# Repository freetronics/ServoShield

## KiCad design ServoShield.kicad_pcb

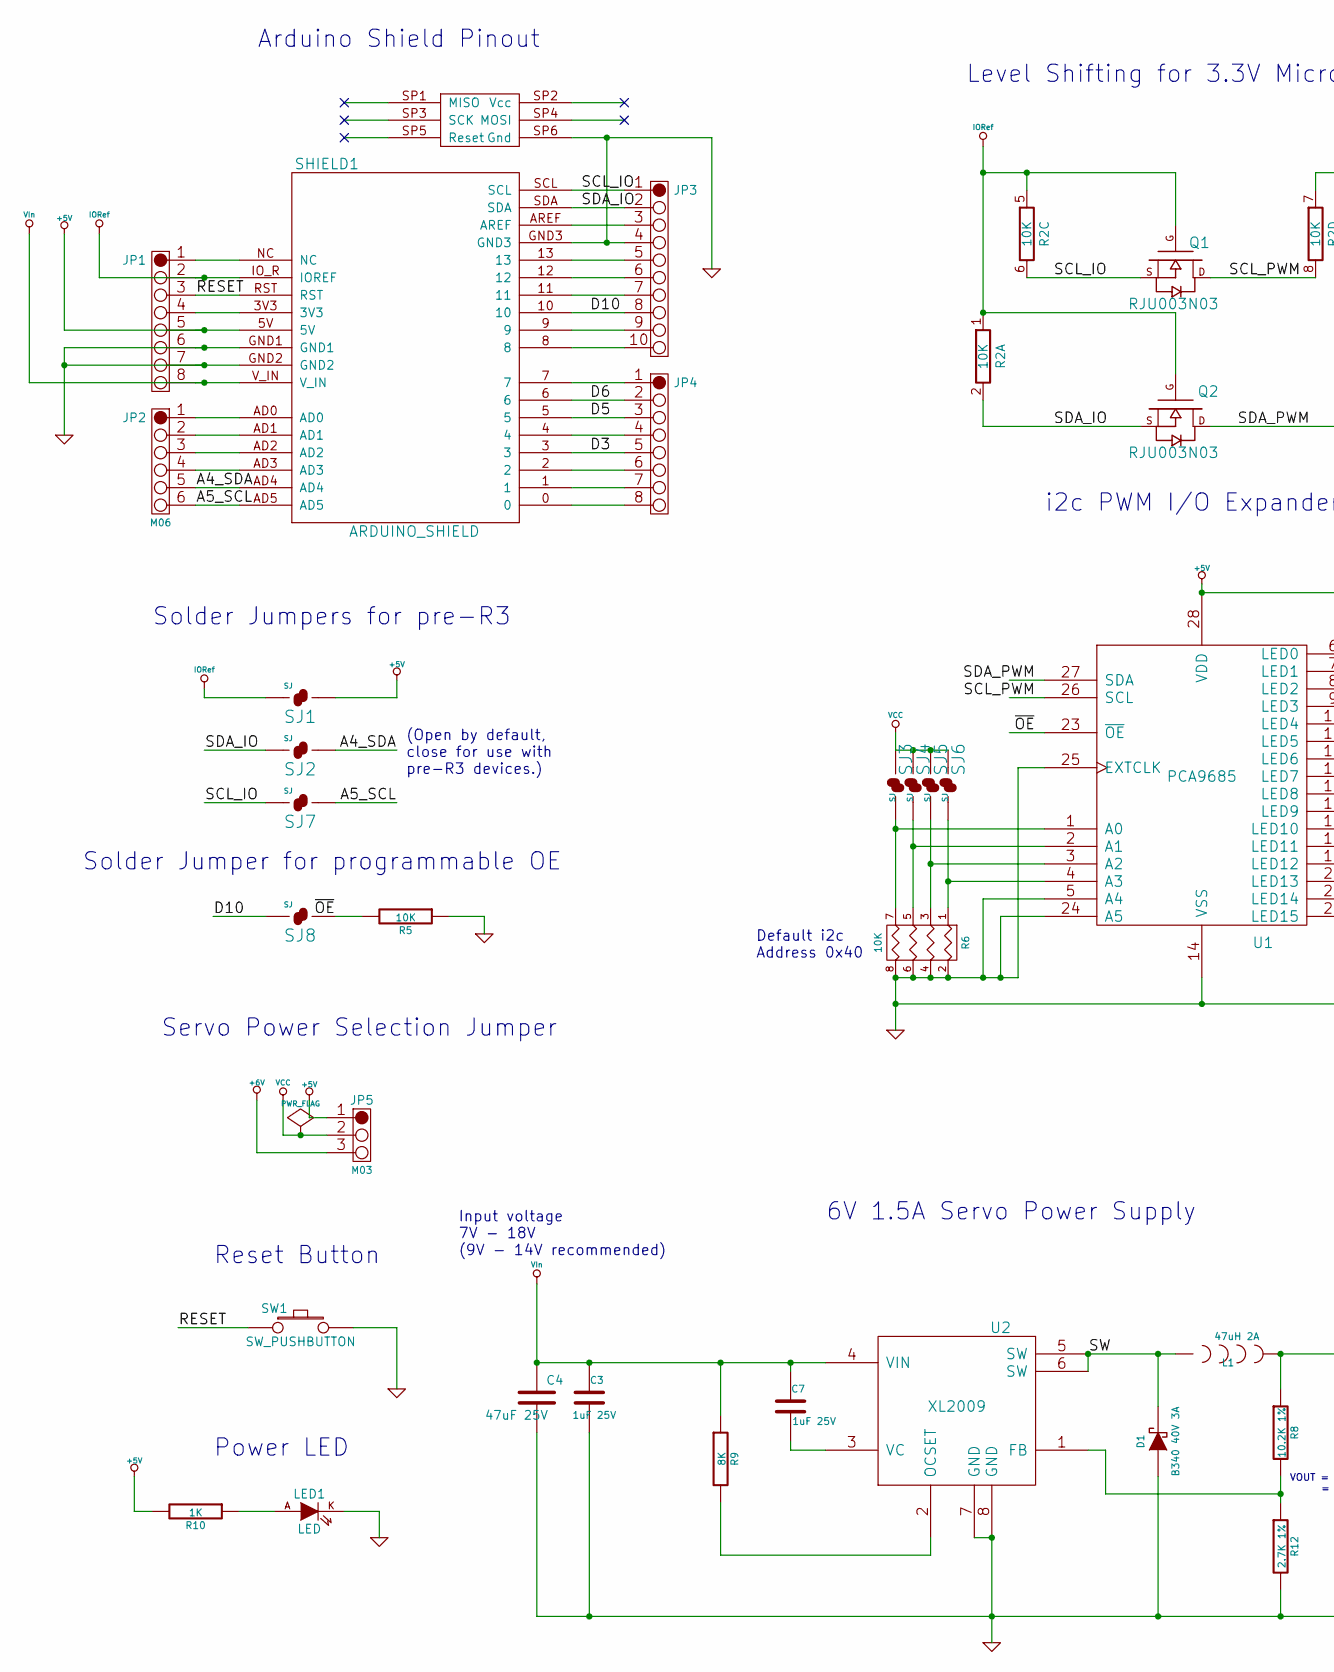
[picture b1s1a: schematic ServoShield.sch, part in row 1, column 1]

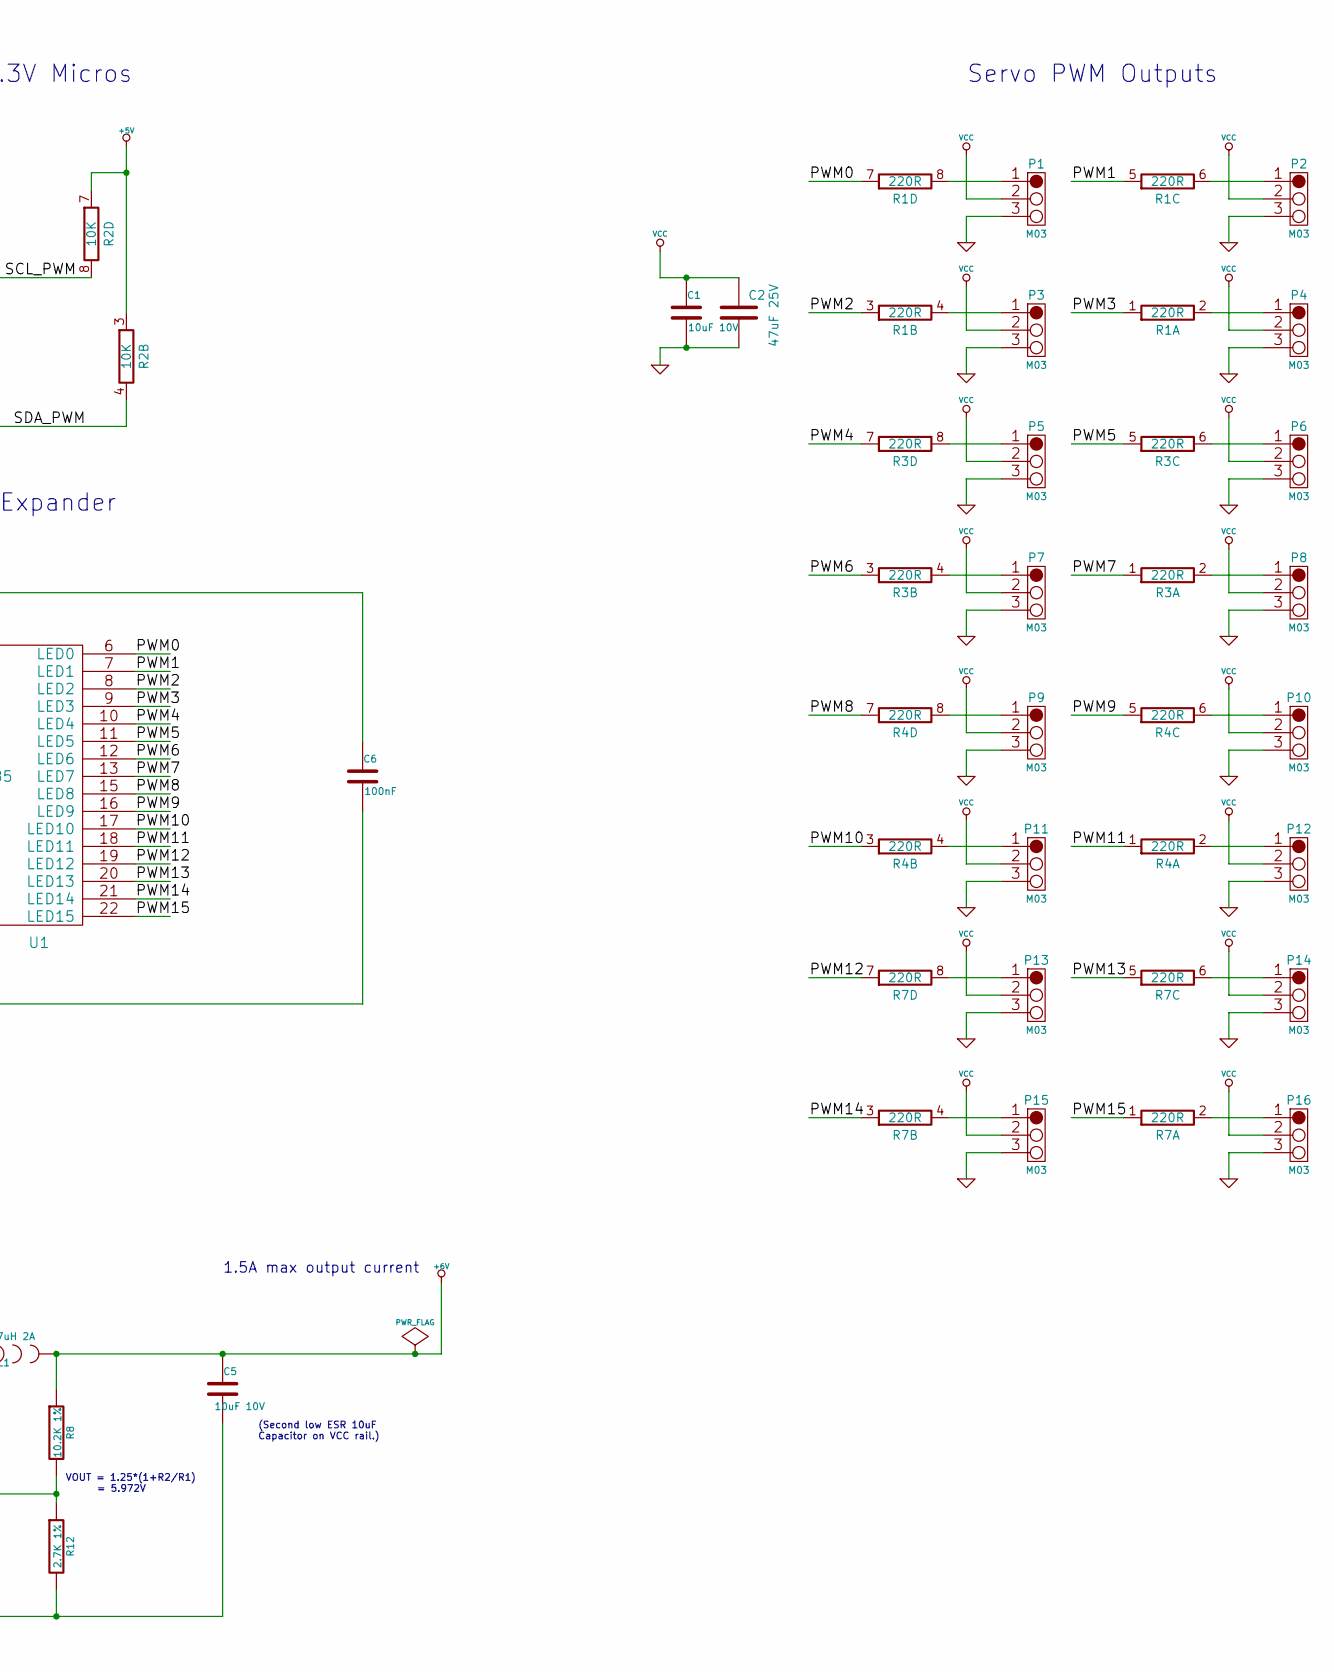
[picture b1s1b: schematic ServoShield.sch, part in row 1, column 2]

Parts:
C1, C5: 10uF 10V; 1210
C2, C4: 47uF 25V; CAP_ELECTRO_SMD_6.6mm
C3, C7: 1uF 25V; 0603_CAP
C6: 100nF; 0603_CAP
D1: B340 40V 3A; DIODE_SMC
JP1, JP4: M08; 1X08
JP2: M06; 1X06
JP3: M10; 1X10
JP5: M03; 1X03
L1: 47uH 2A; IND_CDRH125
LED1: LED; LED-0603
P1, P2, P3, P4, P5, P6, P7, P8, P9, P10, P11, P12, P13, P14, P15, P16: M03; 1X03
Q1, Q2: RJU003N03; SOT323_FET
R1, R3, R4, R7: 220R; RES_CAY16
R2, R6: 10K; RES_CAY16
R5: 10K; 0603
R8: 10.2K 1%; 0603
R9: 8K; 0603
R10: 1K; 0603
R12: 2.7K 1%; 0603
SHIELD1: ARDUINO_SHIELD
SJ1, SJ2, SJ3, SJ4, SJ5, SJ6, SJ7, SJ8: SJ; SJ_OPEN
SW1: SW_PUSHBUTTON; SW_PUSHBUTTON_TINY_2PIN
U1: PCA9685; SSOP28_4mm
U2: XL2009; SO08_4mm

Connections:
+5V: C6.1, JP1.5, JP5.1, R2.3 (7), R2.7, R10.2, SHIELD1.5V, SJ1.2, U1.28 (VDD)
+6V: C5.1, JP5.3, L1.2, R8.1
/A4_SDA: JP2.5, SHIELD1.AD4, SJ2.2
/A5_SCL: JP2.6, SHIELD1.AD5, SJ7.2
/D3: JP4.5, SHIELD1.3
/D5: JP4.3, SHIELD1.5
/D6: JP4.2, SHIELD1.6
/D10: JP3.8, SHIELD1.10, SJ8.1
/PWM0: R1.7, U1.6 (LED0)
/PWM1: R1.5 (7), U1.7 (LED1)
/PWM2: R1.3 (7), U1.8 (LED2)
/PWM3: R1.1 (7), U1.9 (LED3)
/PWM4: R3.7, U1.10 (LED4)
/PWM5: R3.5 (7), U1.11 (LED5)
/PWM6: R3.3 (7), U1.12 (LED6)
/PWM7: R3.1 (7), U1.13 (LED7)
/PWM8: R4.7, U1.15 (LED8)
/PWM9: R4.5 (7), U1.16 (LED9)
/PWM10: R4.3 (7), U1.17 (LED10)
/PWM11: R4.1 (7), U1.18 (LED11)
/PWM12: R7.7, U1.19 (LED12)
/PWM13: R7.5 (7), U1.20 (LED13)
/PWM14: R7.3 (7), U1.21 (LED14)
/PWM15: R7.1 (7), U1.22 (LED15)
/RESET: JP1.3, SHIELD1.RST, SW1.1
/SCL_IO: JP3.1, Q1.S, R2.6 (8), SHIELD1.SCL, SJ7.1
/SCL_PWM: Q1.D, R2.8, U1.26 (SCL)
/SDA_IO: JP3.2, Q2.S, R2.2 (8), SHIELD1.SDA, SJ2.1
/SDA_PWM: Q2.D, R2.4 (8), U1.27 (SDA)
/SW: D1.K, L1.1, U2.5 (SW), U2.6 (SW)
/~OE: R5.2, SJ8.2, U1.23 (~OE)
GND: C1.2, C2.2, C3.2, C4.2, C5.2, C6.2, D1.A, JP1.6, JP1.7, JP3.4, LED1.K, P1.3, P2.3, P3.3, P4.3, P5.3, P6.3, P7.3, P8.3, P9.3, P10.3, P11.3, P12.3, P13.3, P14.3, P15.3, P16.3, R5.1, R6.2 (R1), R6.4 (R1), R6.6 (R3), R6.8 (R4), R12.2, SHIELD1.GND1, SHIELD1.GND2, SHIELD1.GND3, SHIELD1.SP6 (Gnd), SW1.2, U1.5 (A4), U1.14 (VSS), U1.24 (A5), U1.25 (EXTCLK), U2.7 (GND), U2.8 (GND)
IORef: JP1.2, Q1.G, Q2.G, R2.1 (7), R2.5 (7), SHIELD1.IO_R (IOREF), SJ1.1
unnamed: C7.2, U2.3 (VC)
unnamed: JP1.1, SHIELD1.NC
unnamed: JP1.4, SHIELD1.3V3
unnamed: JP2.1, SHIELD1.AD0
unnamed: JP2.2, SHIELD1.AD1
unnamed: JP2.3, SHIELD1.AD2
unnamed: JP2.4, SHIELD1.AD3
unnamed: JP3.3, SHIELD1.AREF
unnamed: JP3.5, SHIELD1.13
unnamed: JP3.6, SHIELD1.12
unnamed: JP3.7, SHIELD1.11
unnamed: JP3.9, SHIELD1.9
unnamed: JP3.10, SHIELD1.8
unnamed: JP4.1, SHIELD1.7
unnamed: JP4.4, SHIELD1.4
unnamed: JP4.6, SHIELD1.2
unnamed: JP4.7, SHIELD1.1
unnamed: JP4.8, SHIELD1.0
unnamed: LED1.A, R10.1
unnamed: P1.1, R1.8
unnamed: P2.1, R1.6 (8)
unnamed: P3.1, R1.4 (8)
unnamed: P4.1, R1.2 (8)
unnamed: P5.1, R3.8
unnamed: P6.1, R3.6 (8)
unnamed: P7.1, R3.4 (8)
unnamed: P8.1, R3.2 (8)
unnamed: P9.1, R4.8
unnamed: P10.1, R4.6 (8)
unnamed: P11.1, R4.4 (8)
unnamed: P12.1, R4.2 (8)
unnamed: P13.1, R7.8
unnamed: P14.1, R7.6 (8)
unnamed: P15.1, R7.4 (8)
unnamed: P16.1, R7.2 (8)
unnamed: R6.1, SJ6.1, U1.4 (A3)
unnamed: R6.3 (P2), SJ5.1, U1.3 (A2)
unnamed: R6.5 (P3), SJ4.1, U1.2 (A1)
unnamed: R6.7 (P4), SJ3.1, U1.1 (A0)
unnamed: R9.2, U2.2 (OCSET)
unnamed: R8.2, R12.1, U2.1 (FB)
VCC: C1.1, C2.1, JP5.2, P1.2, P2.2, P3.2, P4.2, P5.2, P6.2, P7.2, P8.2, P9.2, P10.2, P11.2, P12.2, P13.2, P14.2, P15.2, P16.2, SJ3.2, SJ4.2, SJ5.2, SJ6.2
VIn: C3.1, C4.1, C7.1, JP1.8, R9.1, SHIELD1.V_IN, U2.4 (VIN)

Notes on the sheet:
i2c PWM I/O Expander
Arduino Shield Pinout
Level Shifting for 3.3V Micros
Solder Jumpers for pre-R3
(Open by default, close for use with pre-R3 devices.)
Servo Power Selection Jumper
6V 1.5A Servo Power Supply
1.5A max output current
(Second low ESR 10uF Capacitor on VCC rail.)
Input voltage 7V - 18V (9V - 14V recommended)
Servo PWM Outputs
Reset Button
Solder Jumper for programmable OE
VOUT = 1.25*(1+R2/R1) = 5.972V
Default i2c Address 0x40
Power LED

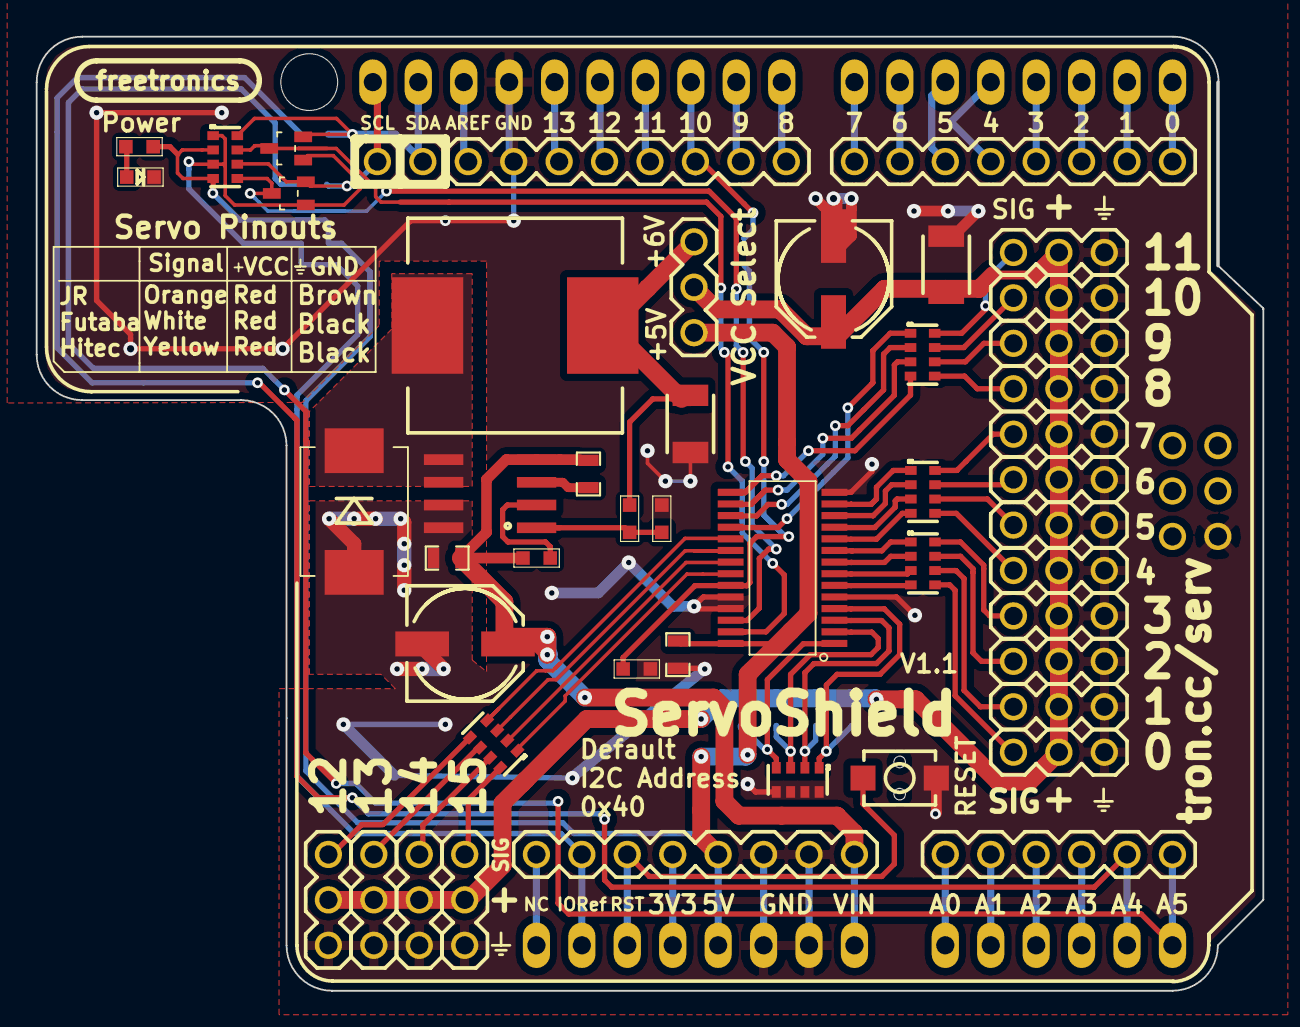
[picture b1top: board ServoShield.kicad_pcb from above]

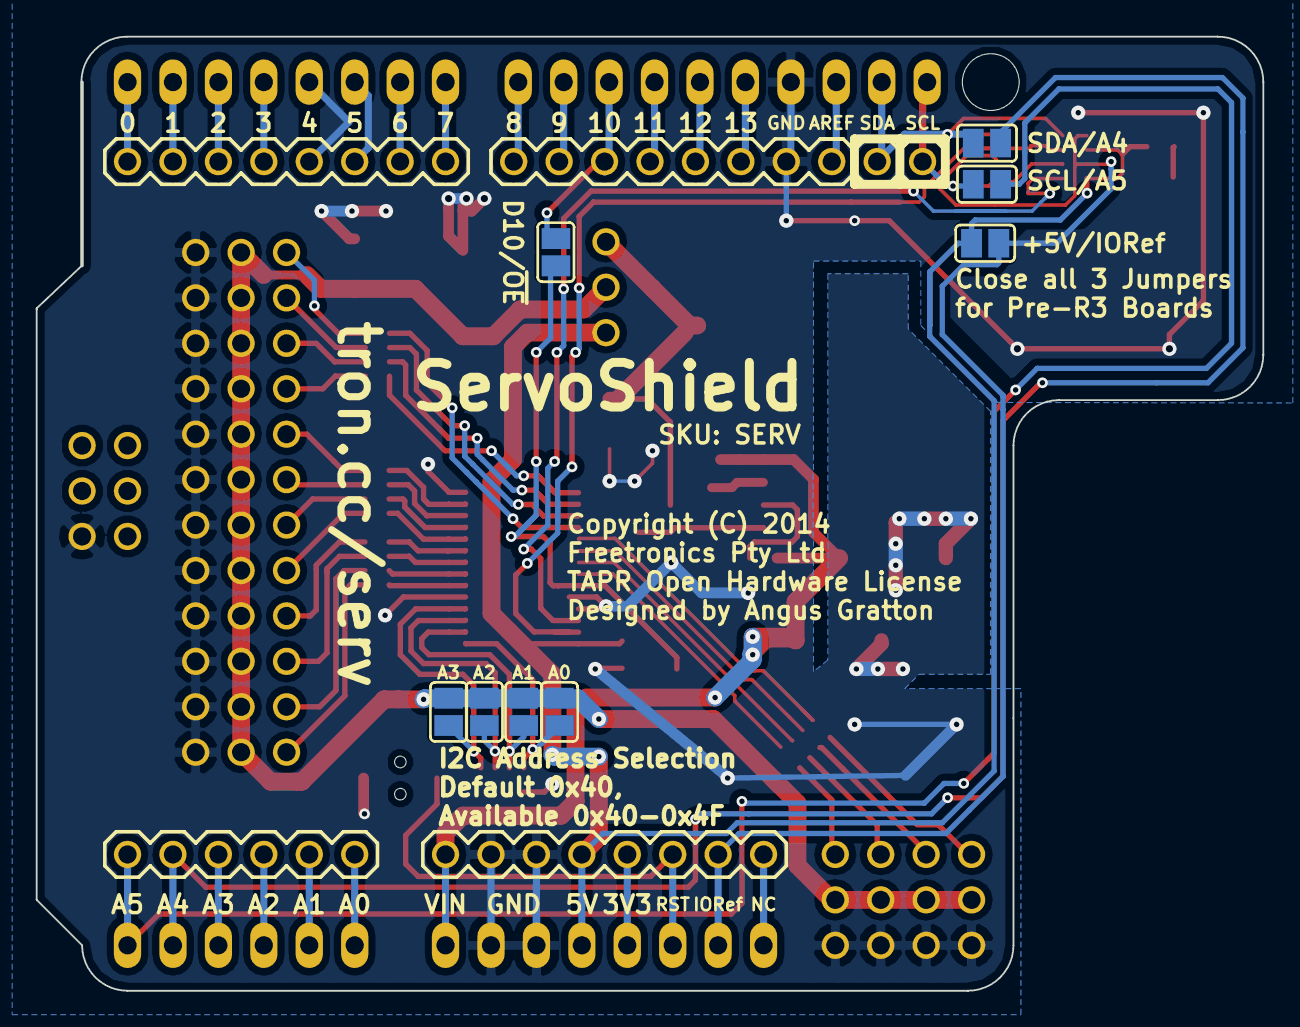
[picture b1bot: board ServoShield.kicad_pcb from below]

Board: 2 copper layers, 68.5 x 53.2 mm, 60 parts (8 on the bottom side), 76 nets.

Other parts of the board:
LOGO_FREETRONICS_SMALL: val**; LOGO_FREETRONICS_MIDSIZE
LOGO_GND_SILKSCREEN: VAL**; LOGO_GND_SILKSCREEN
LOGO_GND_SILKSCREEN#2, LOGO_GND_SILKSCREEN#3: VAL**; LOGO_GND_SILKSCREEN

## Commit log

2014-10-08 Initial routing pass
2014-10-21 Completed v1.0
2014-10-21 Add gitignore
2014-10-21 Such schematic PDF. Wow
2014-11-20 Small tweaks
2014-11-25 V1.1: Add power LED, fix SSOP footprint for PCA9685
2014-12-02 Small V1.1 silkscreen cleanup, new library revision

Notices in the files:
ServoShield.kicad_pcb:
Copyright (C) 2014
TAPR Open Hardware License
ServoShield.sch:
Licensed under TAPR Open Hardware License
Copyright (C) 2014 Freetronics Pty Ltd
